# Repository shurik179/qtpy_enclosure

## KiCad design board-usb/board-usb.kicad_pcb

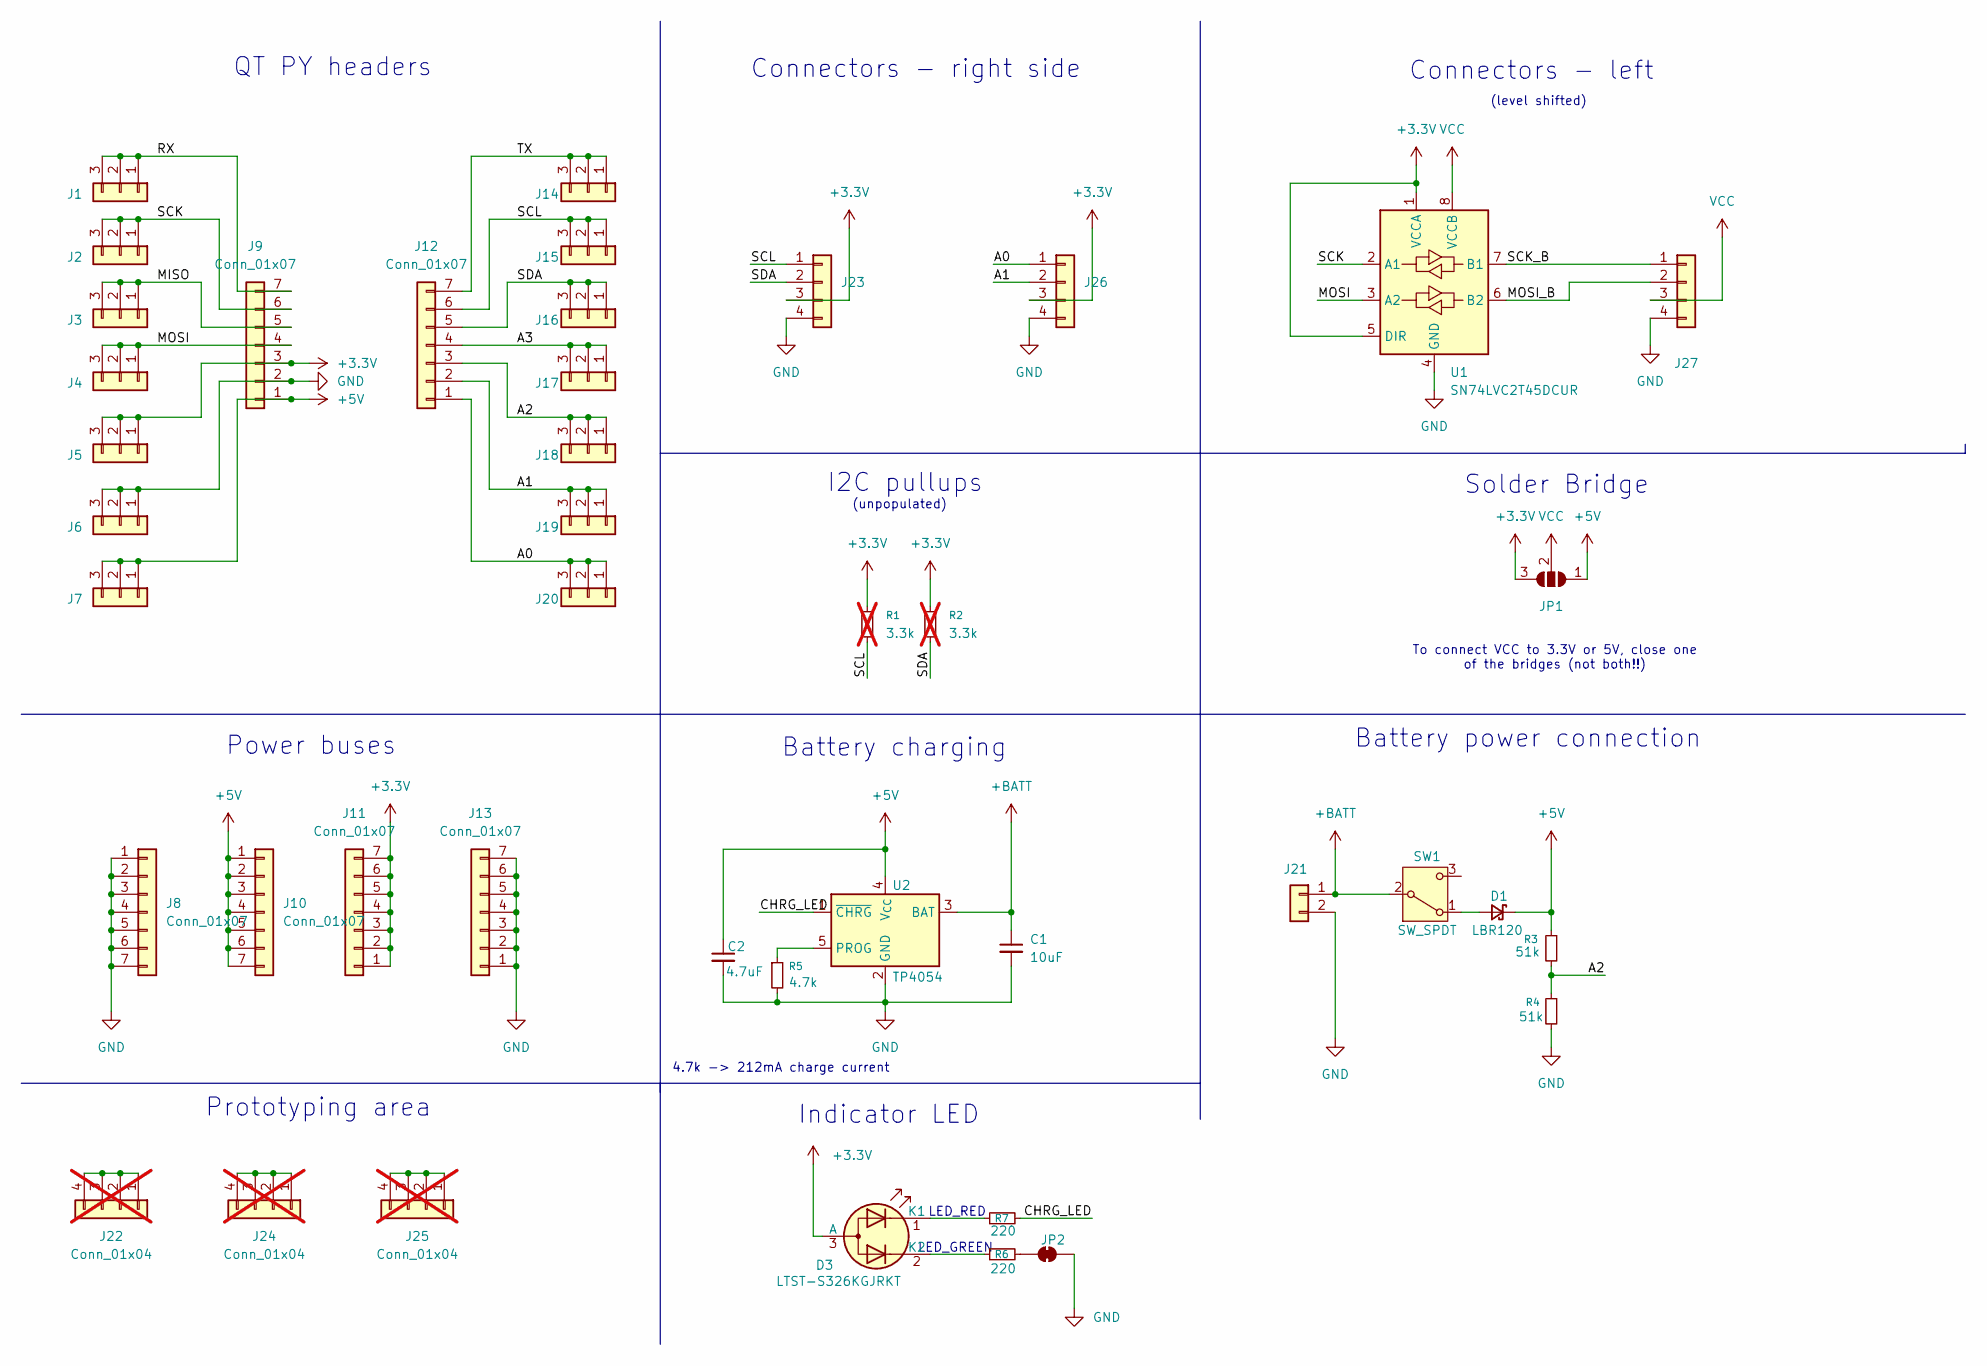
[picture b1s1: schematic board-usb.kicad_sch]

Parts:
C1: 10uF; C_0603_1608Metric
C2: 4.7uF; C_0603_1608Metric
D1: LBR120; D_SOD-123; LCSC C130880
D3: LTST-S326KGJRKT; LED_LiteOn_LTST-S326; LCSC C125116
J1, J2, J3, J4, J5, J6, J7, J14, J15, J16, J17, J18, J19, J20: Conn_01x03; connector-3p-generic-nosilk
J8, J10, J11, J13: Conn_01x07; connector-7p-generic-nosilk
J9, J12: Conn_01x07; connector-7p-generic-nosilk; LCSC C22438157
J21: Conn_01x02; JST_PH_B2B-PH-K_1x02_P2.00mm_Vertical
J22, J24, J25: Conn_01x04; connector-4p-generic-nosilk; not fitted
J23, J26: Conn_01x04; JST_PH_B4B-PH-K_1x04_P2.00mm_Vertical
J27: Conn_01x04; TerminalBlock_KFR141R_2x04_P2.54mm
JP1: SolderJumper_3_Open; SolderJumper-3_P2.0mm_Open_TrianglePad1.0x1.5mm
JP2: SolderJumper_2_Bridged; SolderJumper-2_P1.3mm_Bridged_RoundedPad1.0x1.5mm
R1, R2: 3.3k; R_1206_3216Metric_Pad1.30x1.75mm_HandSolder; not fitted
R3, R4: 51k; R_0603_1608Metric; LCSC C23196
R5: 4.7k; R_0603_1608Metric
R6, R7: 220; R_0603_1608Metric
SW1: SW_SPDT; SW_Slide_SPDT_Angled_SK12D07VG6
U1: SN74LVC2T45DCUR; VSSOP-8_2.3x2mm_P0.5mm; LCSC C15741
U2: TP4054; TSOT-23-5; LCSC C668215

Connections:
+3.3V: D3.3 (A), J5.1, J5.2, J5.3, J9.3, J11.1, J11.2, J11.3, J11.4, J11.5, J11.6, J11.7, J23.3, J26.3, JP1.3 (B), R1.1, R2.1, U1.1 (VCCA), U1.5 (DIR)
+5V: C2.1, D1.1 (K), J7.1, J7.2, J7.3, J9.1, J10.1, J10.2, J10.3, J10.4, J10.5, J10.6, J10.7, JP1.1 (A), R3.1, U2.4 (V_{CC})
+BATT: C1.1, J21.1, SW1.2 (B), U2.3 (BAT)
/A0: J12.1, J20.1, J20.2, J20.3, J26.1
/A1: J12.2, J19.1, J19.2, J19.3, J26.2
/A2: J12.3, J18.1, J18.2, J18.3, R3.2, R4.1
/A3: J12.4, J17.1, J17.2, J17.3
/CHRG_LED: R7.2, U2.1 (~CHRG)
/MISO: J3.1, J3.2, J3.3, J9.5
/MOSI: J4.1, J4.2, J4.3, J9.4, U1.3 (A2)
/MOSI_B: J27.2, U1.6 (B2)
/RX: J1.1, J1.2, J1.3, J9.7
/SCK: J2.1, J2.2, J2.3, J9.6, U1.2 (A1)
/SCK_B: J27.1, U1.7 (B1)
/SCL: J12.6, J15.1, J15.2, J15.3, J23.1, R1.2
/SDA: J12.5, J16.1, J16.2, J16.3, J23.2, R2.2
/TX: J12.7, J14.1, J14.2, J14.3
GND: C1.2, C2.2, J6.1, J6.2, J6.3, J8.1, J8.2, J8.3, J8.4, J8.5, J8.6, J8.7, J9.2, J13.1, J13.2, J13.3, J13.4, J13.5, J13.6, J13.7, J21.2, J23.4, J26.4, J27.4, JP2.1 (A), R4.2, R5.2, U1.4 (GND), U2.2 (GND)
unnamed: D1.2 (A), SW1.1 (A)
unnamed: D3.1 (K1), R7.1
unnamed: D3.2 (K2), R6.1
unnamed: J22.1, J22.2, J22.3, J22.4
unnamed: J24.1, J24.2, J24.3, J24.4
unnamed: J25.1, J25.2, J25.3, J25.4
unnamed: JP2.2 (B), R6.2
unnamed: R5.1, U2.5 (PROG)
VCC: J27.3, JP1.2 (C), U1.8 (VCCB)

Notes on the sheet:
Indicator LED
Battery power connection
I2C pullups
LED_GREEN
(level shifted)
4.7k -> 212mA charge current
Prototyping area
Solder Bridge
Connectors - left
(unpopulated)
Power buses
To connect VCC to 3.3V or 5V, close one of the bridges (not both!!)
QT PY headers
LED_RED
Battery charging
Connectors - right side

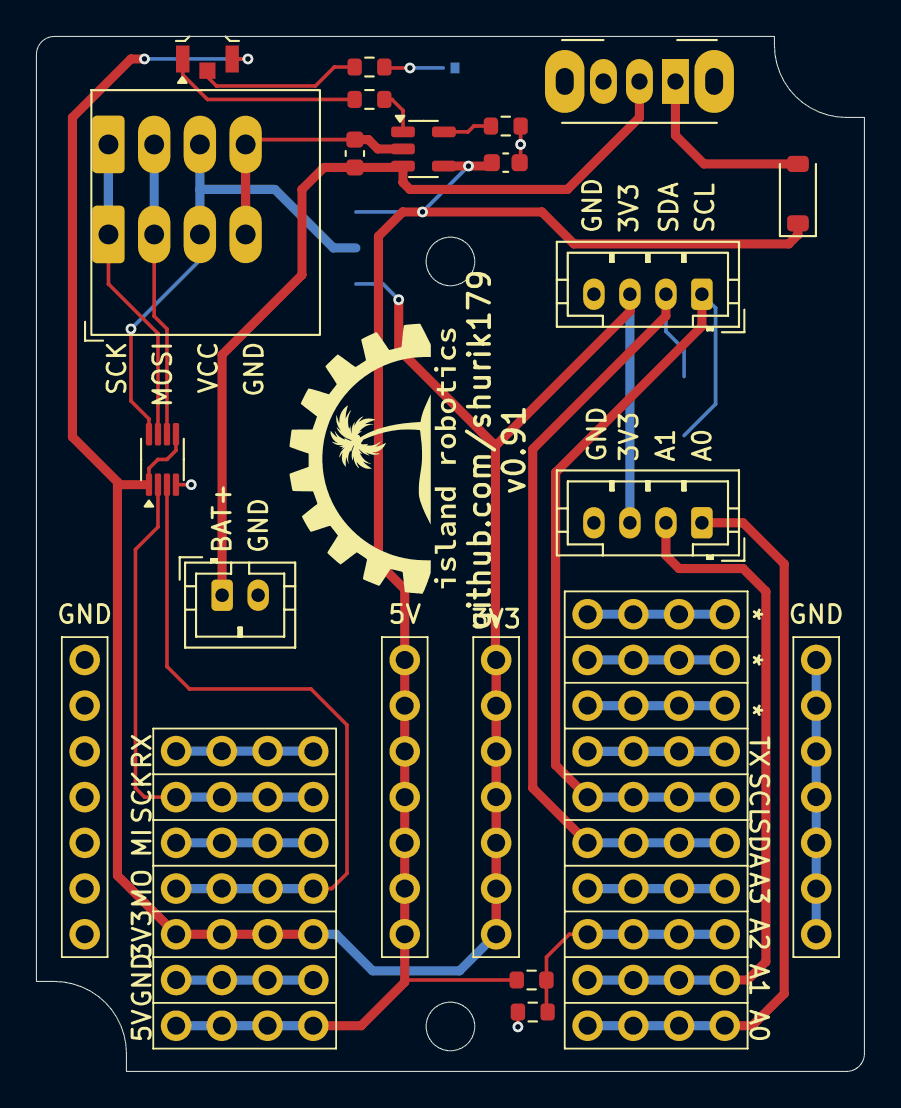
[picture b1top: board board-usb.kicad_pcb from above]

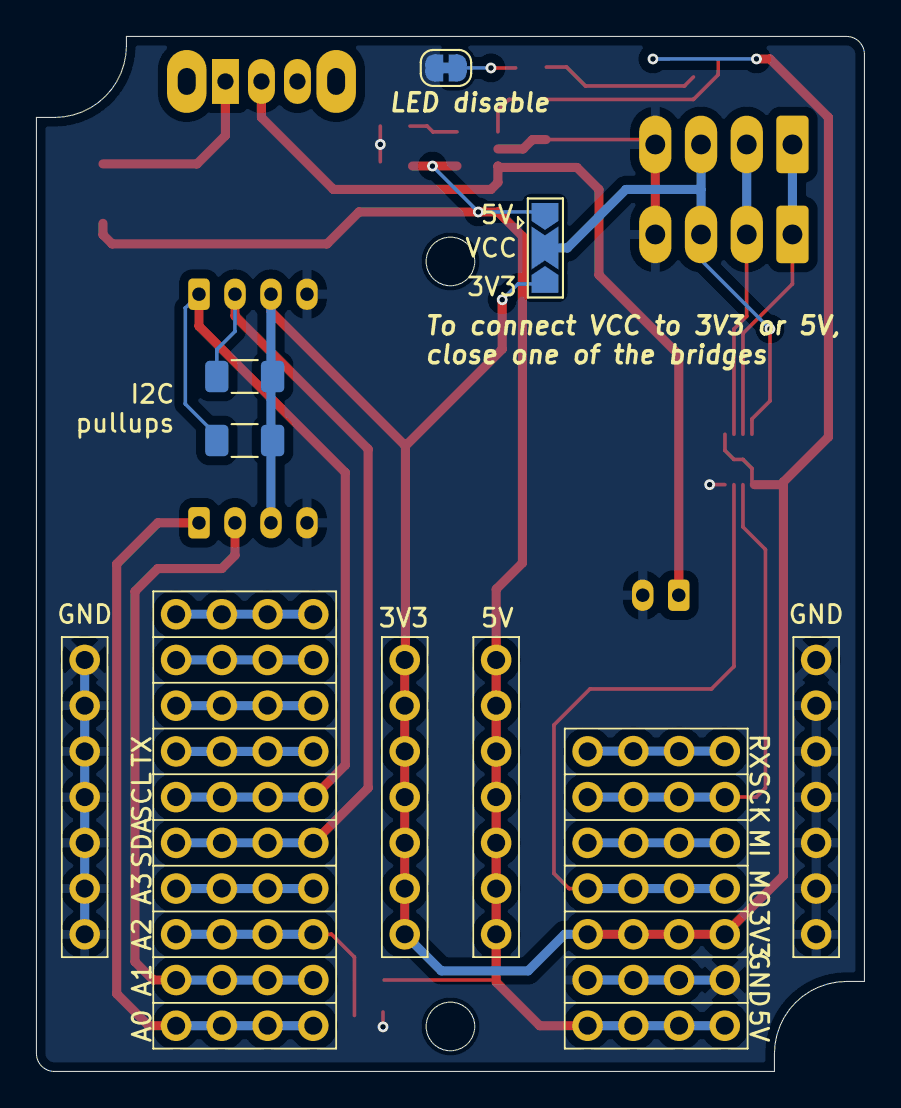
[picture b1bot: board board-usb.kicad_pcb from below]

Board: 2 copper layers, 46.0 x 57.5 mm, 43 parts (4 on the bottom side), 27 nets.

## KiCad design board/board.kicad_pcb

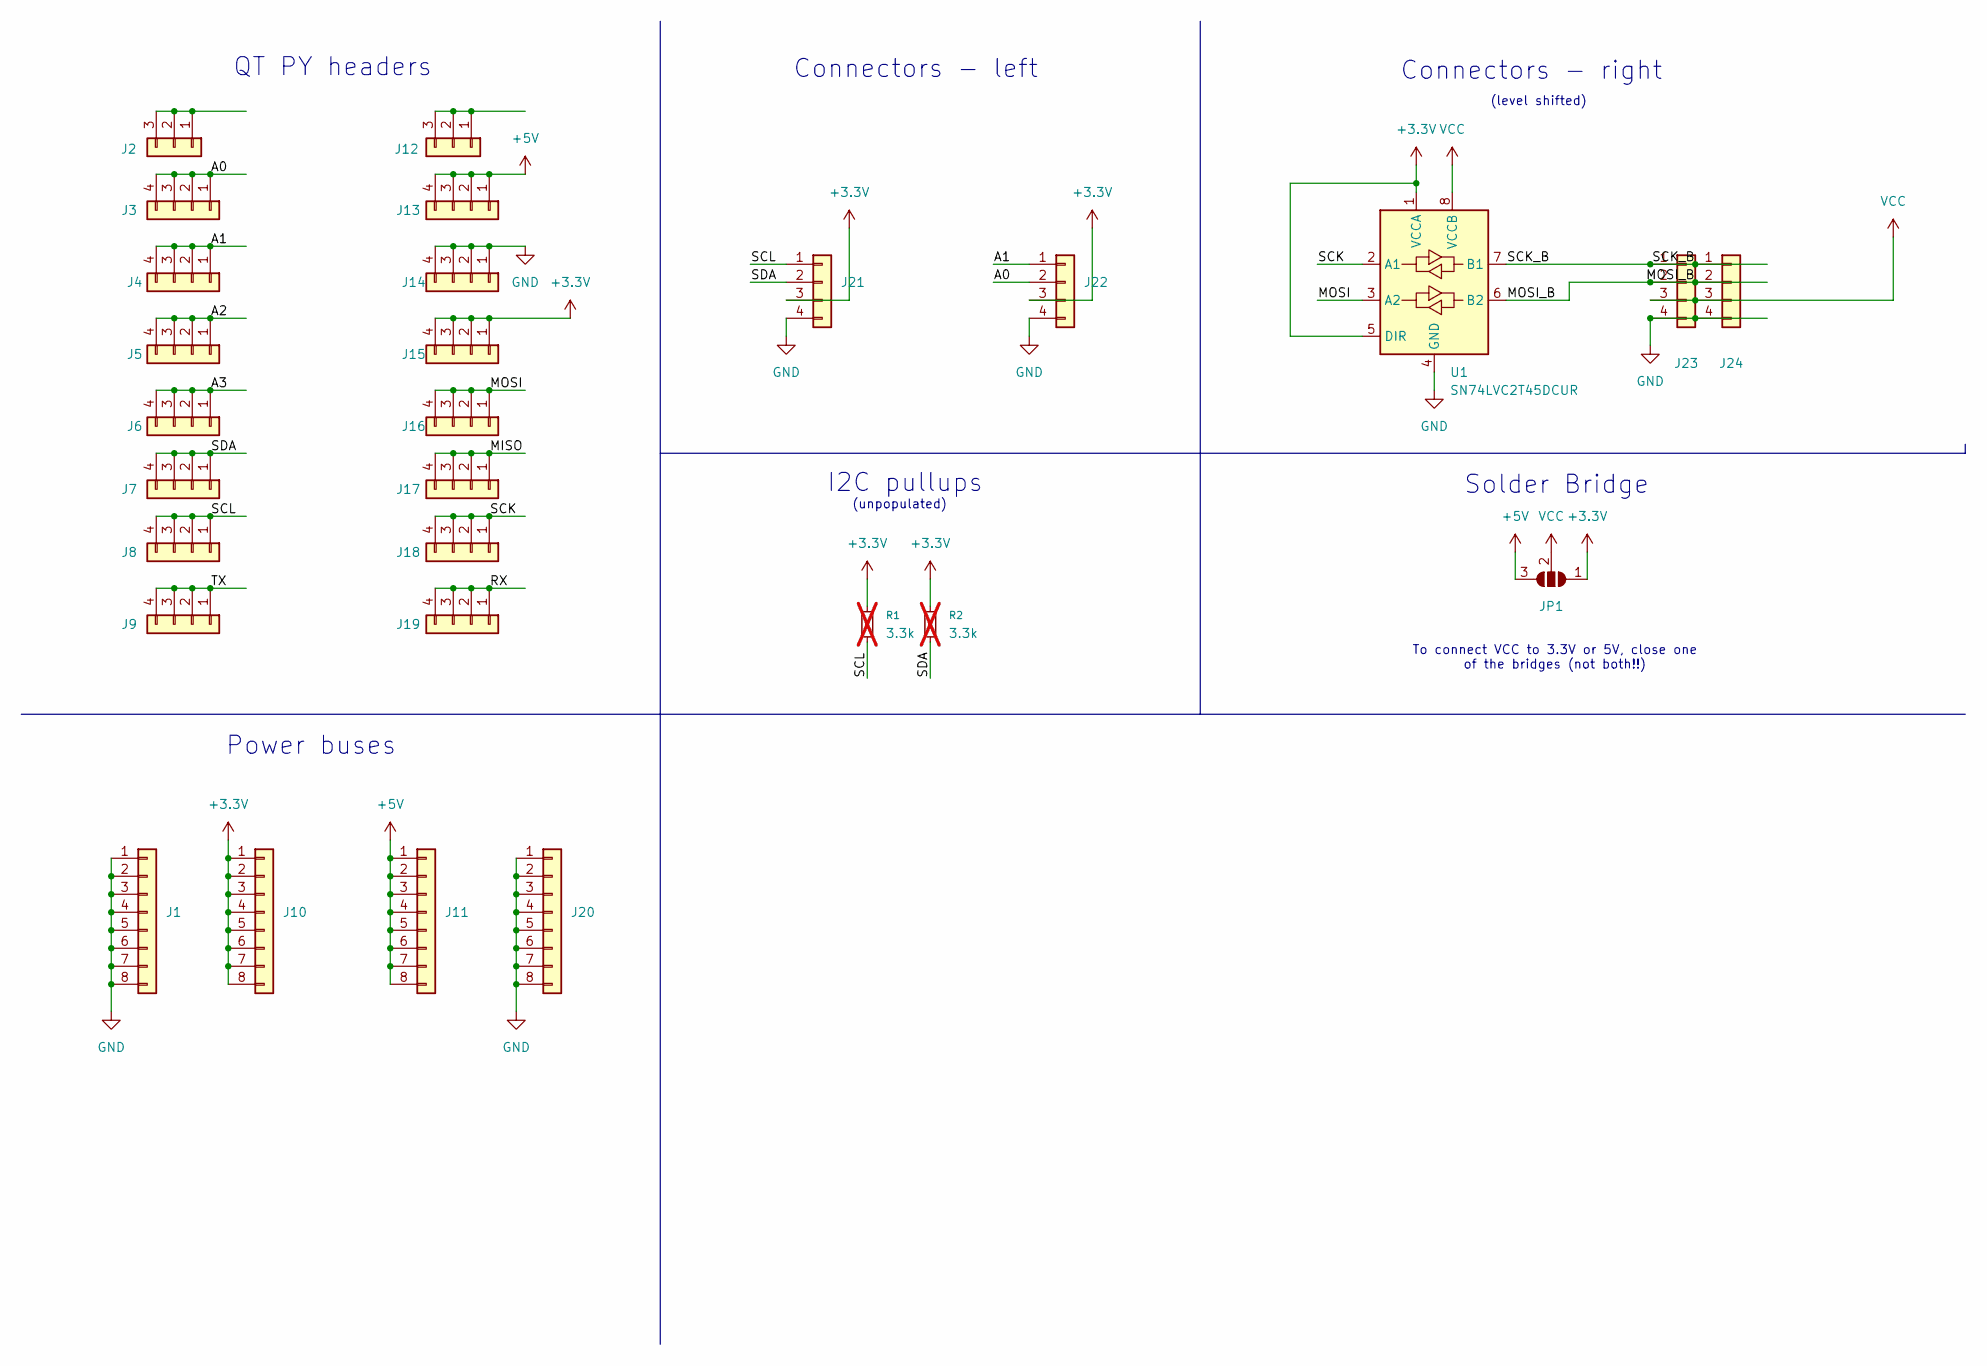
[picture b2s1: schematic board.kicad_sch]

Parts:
J1, J10, J11, J20: Conn_01x08; PinSocket_1x08_P2.54mm_Vertical
J2, J12: Conn_01x03; PinHeader_1x03_P2.54mm_Vertical
J3, J4, J5, J6, J7, J8, J9, J13, J14, J15, J16, J17, J18, J19, J23, J24: Conn_01x04; PinHeader_1x04_P2.54mm_Vertical
J21, J22: Conn_01x04; JST_PH_B4B-PH-K_1x04_P2.00mm_Vertical
JP1: SolderJumper_3_Open; SolderJumper-3_P2.0mm_Open_TrianglePad1.0x1.5mm
R1, R2: 3.3k; R_1206_3216Metric_Pad1.30x1.75mm_HandSolder; not fitted
U1: SN74LVC2T45DCUR; VSSOP-8_2.3x2mm_P0.5mm

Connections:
+3.3V: J10.1, J10.2, J10.3, J10.4, J10.5, J10.6, J10.7, J10.8, J15.1, J15.2, J15.3, J15.4, J21.3, J22.3, JP1.1 (A), R1.1, R2.1, U1.1 (VCCA), U1.5 (DIR)
+5V: J11.1, J11.2, J11.3, J11.4, J11.5, J11.6, J11.7, J11.8, J13.1, J13.2, J13.3, J13.4, JP1.3 (B)
/A0: J3.1, J3.2, J3.3, J3.4, J22.2
/A1: J4.1, J4.2, J4.3, J4.4, J22.1
/A2: J5.1, J5.2, J5.3, J5.4
/A3: J6.1, J6.2, J6.3, J6.4
/MISO: J17.1, J17.2, J17.3, J17.4
/MOSI: J16.1, J16.2, J16.3, J16.4, U1.3 (A2)
/MOSI_B: J23.2, J24.2, U1.6 (B2)
/RX: J19.1, J19.2, J19.3, J19.4
/SCK: J18.1, J18.2, J18.3, J18.4, U1.2 (A1)
/SCK_B: J23.1, J24.1, U1.7 (B1)
/SCL: J8.1, J8.2, J8.3, J8.4, J21.1, R1.2
/SDA: J7.1, J7.2, J7.3, J7.4, J21.2, R2.2
/TX: J9.1, J9.2, J9.3, J9.4
GND: J1.1, J1.2, J1.3, J1.4, J1.5, J1.6, J1.7, J1.8, J14.1, J14.2, J14.3, J14.4, J20.1, J20.2, J20.3, J20.4, J20.5, J20.6, J20.7, J20.8, J21.4, J22.4, J23.4, J24.4, U1.4 (GND)
unnamed: J2.1, J2.2, J2.3
unnamed: J12.1, J12.2, J12.3
VCC: J23.3, J24.3, JP1.2 (C), U1.8 (VCCB)

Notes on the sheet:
I2C pullups
(level shifted)
Solder Bridge
Connectors - right
(unpopulated)
Power buses
To connect VCC to 3.3V or 5V, close one of the bridges (not both!!)
QT PY headers
Connectors - left

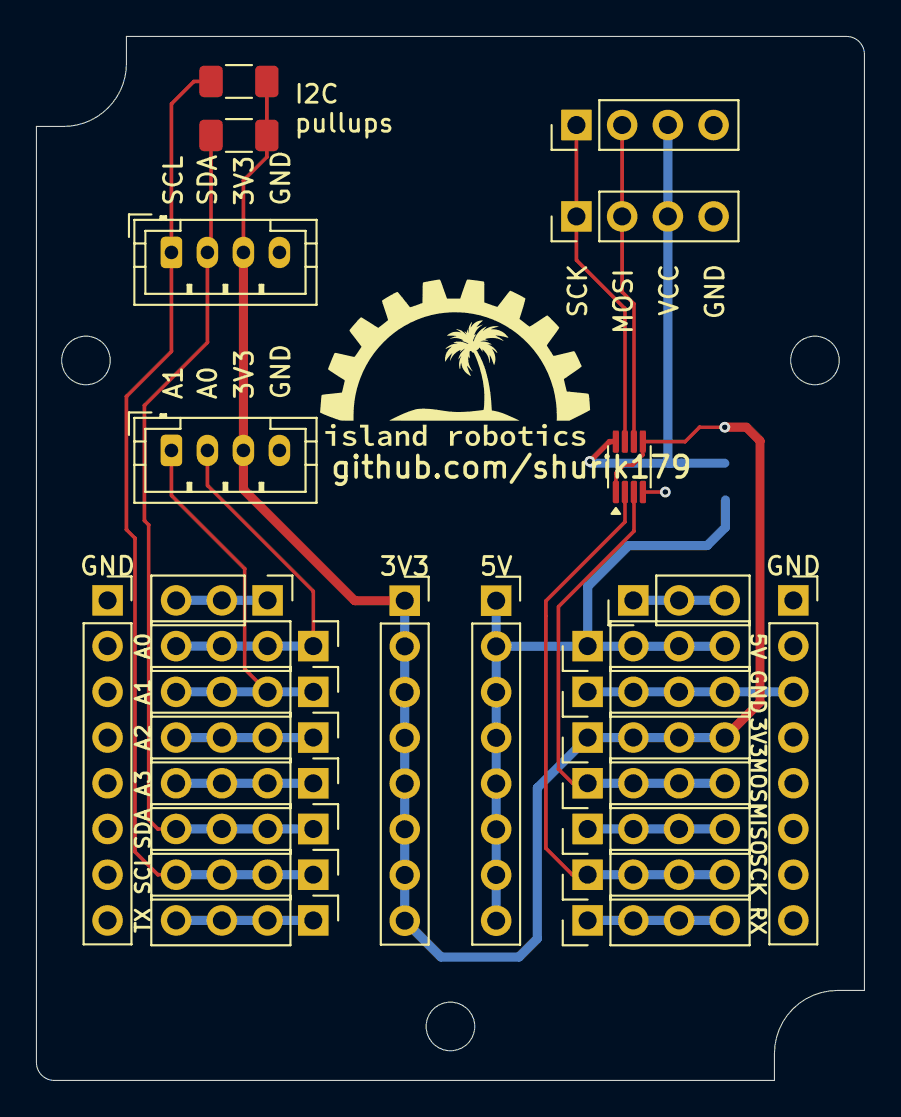
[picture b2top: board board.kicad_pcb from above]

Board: 2 copper layers, 46.0 x 58.0 mm, 28 parts (1 on the bottom side), 19 nets.
